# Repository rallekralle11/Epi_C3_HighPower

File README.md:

# Epi C3 PD
Very narrow ESP32 dev board with high-power switching capabilities as well as USB PD support.

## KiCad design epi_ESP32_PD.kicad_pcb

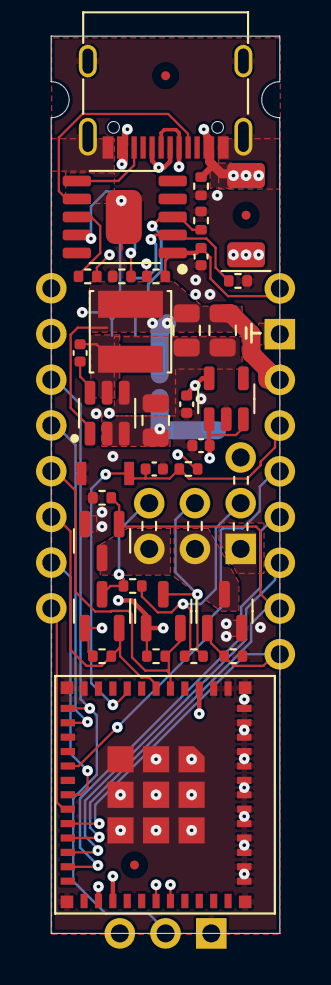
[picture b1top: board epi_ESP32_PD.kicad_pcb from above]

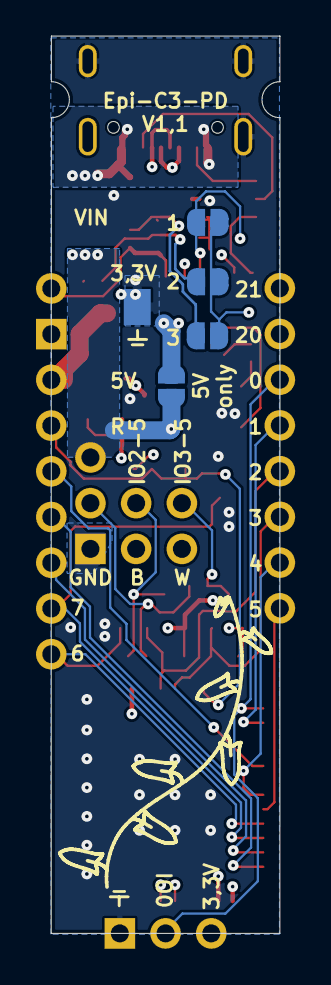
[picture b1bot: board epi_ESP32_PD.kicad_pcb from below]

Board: 4 copper layers, 12.7 x 49.8 mm, 42 parts (5 on the bottom side), 33 nets.

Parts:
C1, C8, C11, C13: 1µF; C_0402_1005Metric
C10: 10µF; C_0805_2012Metric
C15: 100nF; C_0402_1005Metric
C16, C17: 22µF; C_0805_2012Metric
D1: D_Small; D_SOD-128
J1: Conn_01x08; PinHeader_1x08_P2.54mm_Vertical
J2: USB_C_Receptacle_USB2.0; USB_C_Receptacle_G-Switch_GT-USB-7010ASV
J4: Conn_01x01; TestPoint_Pad_3.0x3.0mm
J5: Conn_01x09; PinHeader_1x09_P2.54mm_Vertical
J7: Conn_02x03; PinHeader_2x03_P2.54mm_Horizontal
J8: Conn_01x03; PinHeader_1x03_P2.54mm_Vertical
JP1, JP2, JP3, JP4: Jumper; SolderJumper-2_P1.3mm_Open_RoundedPad1.0x1.5mm
L2: TBD; L_Abracon_ASPI-0425
Q1, Q2, Q3, Q4: Q_NMOS_GSD; SOT-23
R1: TBD; R_0402_1005Metric
R3, R8, R15: 1K; R_0402_1005Metric
R6: 10kΩ; R_0402_1005Metric
R7, R9, R10, R11, R12, R13, R14: 10K; R_0402_1005Metric
RV3: Varistor; R_0402_1005Metric
SW2: SW_MEC_5G; R-668048
U1: ESP32-C3-MINI-1
U2: MIC5219-3.3YM5; SOT-23-5
U3: SOIC-10_3.9x4.9mm_P1mm
U5: AP63205WU; TSOT-23-6

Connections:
+3.3V: C1.2, C8.1, J5.1, J8.1, JP1.1 (A), JP2.1 (A), JP3.2 (B), Q1.1 (G), Q2.1 (G), R1.1, R6.1, R9.2, R11.2, U1.3 (3V3), U2.5 (OUT), U3.1 (VDD)
+5V: C13.2, C16.2, C17.2, J5.3, J7.1, JP4.1 (A), L2.2, R10.2, R12.2, U2.1 (IN), U2.3 (EN), U5.1 (FB)
/buck: C15.2, L2.1, U5.5 (SW)
B: J7.4, Q4.3 (D)
BOOT: J5.6, U1.23 (GPIO9)
D+: J2.A6 (D+), J2.B6 (D+), U1.27 (GPIO19/USB_D+)
D-: J2.A7 (D-), J2.B7 (D-), U1.26 (GPIO18/USB_D-)
EN: C11.2, J5.4, R6.2, SW2.1 (A), U1.8 (EN/CHIP_PU)
GND: C1.1, C8.2, C10.1, C11.1, C13.1, C16.1, C17.1, J2.A1 (GND), J2.A12 (GND), J2.B1 (GND), J2.B12 (GND), J2.S1 (SHIELD), J4.1, J5.2, J7.2, J8.3, Q3.2 (S), Q4.2 (S), R3.1, R8.1, R13.1, R14.1, R15.1, RV3.2, SW2.3 (B), U1.1 (GND), U1.2 (GND), U1.11 (GND), U1.14 (GND), U1.36 (GND), U1.37 (GND), U1.38 (GND), U1.39 (GND), U1.40 (GND), U1.41 (GND), U1.42 (GND), U1.43 (GND), U1.44 (GND), U1.45 (GND), U1.46 (GND), U1.47 (GND), U1.48 (GND), U1.49 (GND), U1.50 (GND), U1.51 (GND), U1.52 (GND), U1.53 (GND), U2.2 (GND), U3.0 (GND), U5.4 (GND)
IO0: J1.3, J8.2, U1.12 (GPIO0/ADC1_CH0/XTAL_32K_P)
IO1: J1.4, U1.13 (GPIO1/ADC1_CH1/XTAL_32K_N)
IO2: J1.5, Q1.2 (S), R9.1, U1.5 (GPIO2/ADC1_CH2)
IO2_5V: J7.3, Q1.3 (D), R10.1
IO3: J1.6, Q2.2 (S), R11.1, U1.6 (GPIO3/ADC1_CH3)
IO3_5V: J7.5, Q2.3 (D), R12.1
IO4: J1.7, U1.18 (GPIO4/ADC1_CH4)
IO5: J1.8, U1.19 (GPIO5/ADC2_CH0)
IO6: J5.9, Q4.1 (G), R13.2, U1.20 (GPIO6)
IO7: J5.8, Q3.1 (G), R14.2, U1.21 (GPIO7)
IO8: J5.7, U1.22 (GPIO8)
IO10: J5.5, U1.16 (GPIO10)
unnamed: J2.A5 (CC1), U3.7 (CC1)
unnamed: J2.B5 (CC2), U3.6 (CC2)
unnamed: JP1.2 (B), R8.2, U3.2 (CFG2)
unnamed: JP2.2 (B), R3.2, U3.3 (CFG3)
unnamed: JP3.1 (A), R15.2, U3.9 (CFG1)
unnamed: R7.2, U3.8 (VBUS)
unnamed: C15.1, U5.6 (BST)
PD: D1.2 (A), J2.A4 (VBUS), J2.A9 (VBUS), J2.B4 (VBUS), J2.B9 (VBUS), R1.2, R7.1, RV3.1
U0RXD: J1.2, U1.30 (GPIO20/U0RXD)
U0TXD: J1.1, U1.31 (GPIO21/U0TXD)
VIN: C10.2, D1.1 (K), J7.0, JP4.2 (B), U5.2 (EN), U5.3 (IN)
W: J7.6, Q3.3 (D)

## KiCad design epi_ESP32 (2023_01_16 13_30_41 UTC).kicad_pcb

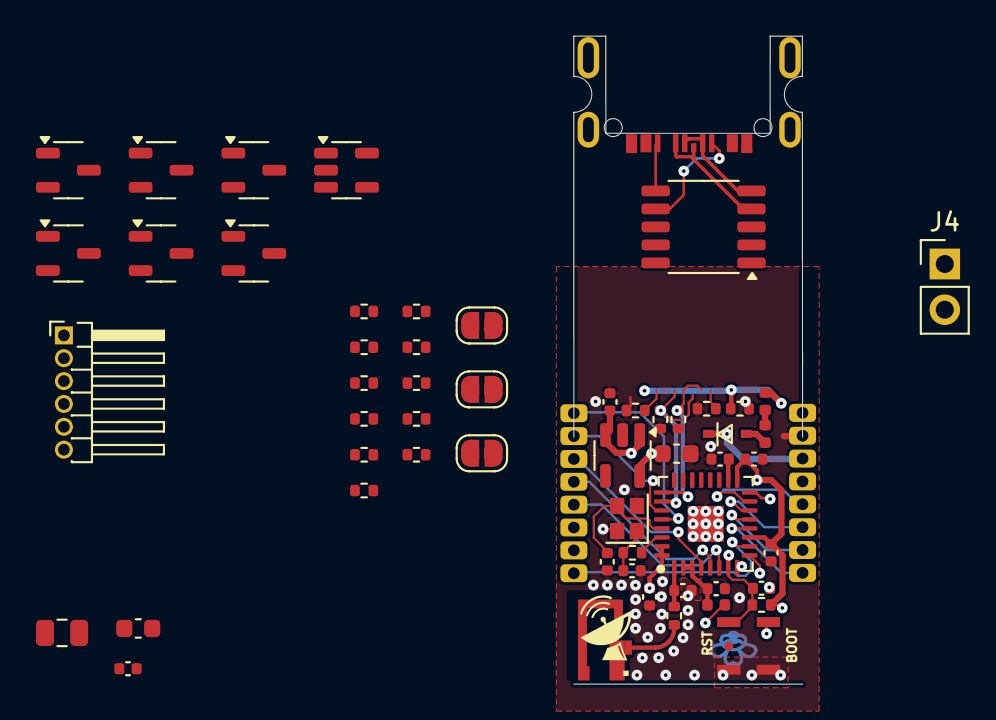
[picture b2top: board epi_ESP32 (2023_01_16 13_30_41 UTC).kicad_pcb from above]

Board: 4 copper layers, 61 parts (0 on the bottom side), 41 nets.

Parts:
AE1: Antenna; 2450AT14A0100001T
C1, C2, C7: 100nF; C_0402_1005Metric
C3, C4, C6: TBD; C_0402_1005Metric
C5, C9, C11, C12, C13: 1µF; C_0402_1005Metric
C8: 1µF; C_0805_2012Metric
C10, C14: 22µF; C_0603_1608Metric
D1: D; SOD323_bättre (2022_12_20 17_46_41 UTC)
DRILL1, DRILL2: NPTH
F1: 500mA; Fuse_0402_1005Metric
FB1, FB2: Ferrite; L_0402_1005Metric
J1, J3: Conn_01x08; PinHeader_1x08_P1.27mm_Vertical
J2: USB_C_Receptacle_USB2.0; USB-C MC-314C-4P16_V2 (2023_01_13 17_48_46 UTC)
J4: Conn_01x02; PinHeader_1x02_P2.54mm_Vertical
J5: Conn_01x06; PinHeader_1x06_P1.27mm_Horizontal
JP1, JP2, JP3: Jumper; SolderJumper-2_P1.3mm_Open_RoundedPad1.0x1.5mm
L1: TBD; R_0402_1005Metric
Q1: Q_PMOS_GDS; SOT-23-3
Q2, Q3, Q4, Q5, Q6: Q_NMOS_GDS; SOT-23-3
R1: 1K; R_0402_1005Metric
R2: 22Ω; R_0402_1005Metric
R3, R4, R5#2, R7, R8, R9, R10, R11, R12: 10K; R_0402_1005Metric
R4#2, R5: 5,1kΩ; R_0402_1005Metric
R6: 10kΩ; R_0402_1005Metric
RV1, RV2, RV3, RV4: Varistor; R_0402_1005Metric
SW1, SW2: SW_MEC_5G; R-668048
U1: ESP32-C3; QFN-32-1EP_5x5mm_P0.5mm_EP3.45x3.45mm
U2: MIC5219-5.0YM5; SOT-23-5
U3: SOIC-10_3.9x4.9mm_P1mm
U4: MIC5219-3.3YM5; SOT-23-5
Y1: Crystal; Crystal_SMD_2016-4Pin_2.0x1.6mm

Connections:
+3.3V: C1.2, C2.2, C5.2, C7.2, C10.2, FB2.1, J3.1, Q3.1 (G), Q4.1 (G), R6.1, R9.2, R11.2, U1.2 (VDD3P3), U1.3 (VDD3P3), U1.11 (VDD3P3_RTC), U1.17 (VDD3P3_CPU), U1.31 (VDDA), U1.32 (VDDA), U4.5 (OUT)
+5V: C14.2, FB1.1, J3.3, R10.2, R12.2, U2.5 (OUT)
B: J5.1, Q2.2 (D)
BOOT: J3.5, SW1.1 (A), U1.15 (GPIO9/BOOT)
D+: J2.A6 (D+), J2.B6 (D+), RV2.2, U1.26 (GPIO19/USB_D+), U3.4 (DP)
D-: J2.A7 (D-), J2.B7 (D-), RV3.2, U1.25 (GPIO18/USB_D-), U3.5 (DM)
EN: C11.2, J3.4, R6.2, SW2.1 (A), U1.7 (CHIP_EN)
GND: C1.1, C2.1, C3.1, C4.1, C5.1, C6.1, C7.1, C8.1, C9.1, C10.1, C11.1, C12.2, C13.1, C14.1, J2.A1 (GND), J2.B12 (GND), J2.S1 (SHIELD), J3.2, J4.2, J5.6, Q2.3 (S), Q5.2 (D), Q6.3 (S), R3.1, R4#2.2, R5.2, R5#2.1, R8.1, RV1.2, RV2.1, RV3.1, RV4.2, SW1.3 (B), SW2.3 (B), U1.33 (GND), U2.2 (GND), U4.2 (GND), Y1.2, Y1.4
IO0: J1.3, U1.4 (XTAL_32K_P/ADC1_CH0)
IO1: J1.4, U1.5 (XTAL_32K_N/ADC1_CH1)
IO2: J1.5, Q3.3 (S), R9.1, U1.6 (GPIO2/ADC1_CH2)
IO2_5V: J5.3, Q3.2 (D), R10.1
IO3: J1.6, Q4.3 (S), R11.1, U1.8 (GPIO3/ADC1_CH3)
IO3_5V: J5.4, Q4.2 (D), R12.1
IO4: J1.7, U1.9 (MTMS/GPIO4/ADC1_CH4)
IO5: J1.8, U1.10 (MTDI/GPIO5/ADC2_CH0)
IO6: J3.8, Q2.1 (G), U1.12 (MTCK/GPIO6)
IO7: J3.7, Q6.1 (G), U1.13 (MTDO/GPIO7)
IO8: J3.6, U1.14 (GPIO8)
IO10: Q5.1 (G), R5#2.2, U1.16 (GPIO10)
unnamed: AE1.1 (A), L1.2
unnamed: C4.2, R2.1, Y1.1
unnamed: D1.2 (A), F1.2
unnamed: F1.1, FB1.2
unnamed: J2.A5 (CC1), U3.7 (CC1)
unnamed: J2.B5 (CC2), U3.6 (CC2)
unnamed: JP1.2 (B), R8.2, U3.2 (CFG2)
unnamed: JP2.2 (B), R3.2, U3.3 (CFG3)
unnamed: JP3.1 (A), U3.9 (CFG1)
unnamed: Q1.1 (G), Q5.3 (S), R4.1
unnamed: C6.2, L1.1, U1.1 (LNA_IN)
unnamed: C12.1, U1.18 (VDD_SPI/GPIO11)
unnamed: C3.2, U1.29 (XTAL_N), Y1.3
unnamed: R2.2, U1.30 (XTAL_P)
unnamed: C8.2, R7.2, U3.8 (VBUS)
unnamed: R1.1, U3.1 (VDD)
U0RXD: J1.2, U1.27 (U0RXD/GPIO20)
U0TXD: J1.1, U1.28 (U0TXD/GPIO21)
VCC: C9.2, C13.2, D1.1 (K), J2.A4 (VBUS), J2.A9 (VBUS), J4.1, JP1.1 (A), JP2.1 (A), JP3.2 (B), Q1.3 (S), R1.2, R4.2, R7.1, RV1.1, RV4.1, U2.1 (IN), U2.3 (EN), U4.1 (IN), U4.3 (EN)
VOUT: J5.5, Q1.2 (D)
W: J5.2, Q6.2 (D)

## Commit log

2024-10-07 init
2024-10-08 designed
2024-10-09 made it pretty
2024-10-10 finishing touches
2024-10-10 cleanup and readme
2024-10-10 little fix
2024-10-11 added a couple debugging jumpers
2024-12-13 revision
